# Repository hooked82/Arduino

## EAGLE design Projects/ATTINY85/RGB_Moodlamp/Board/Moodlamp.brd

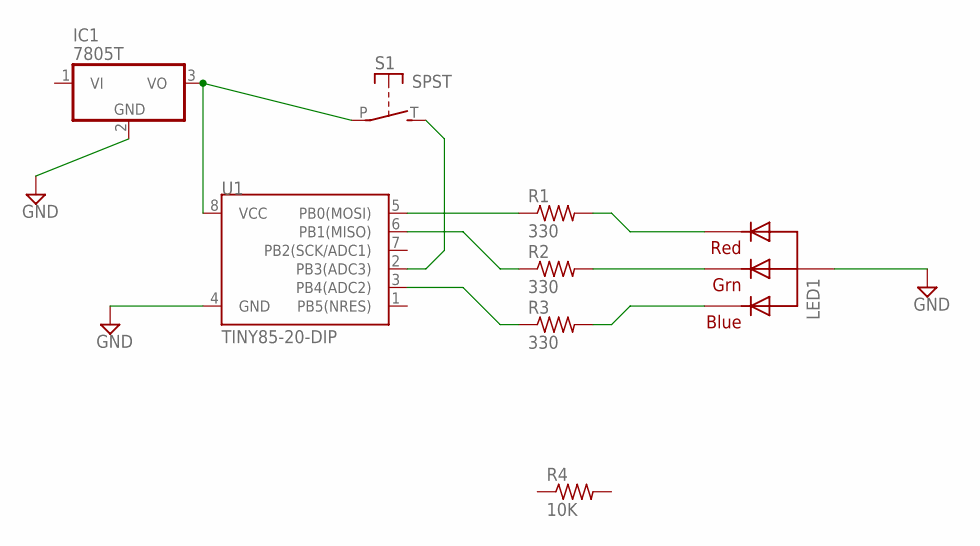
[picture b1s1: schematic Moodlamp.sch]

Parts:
IC1: 7805T; TO220H
LED1: RGBLED_CA-5MM; LED5MMRGB
R1, R2, R3: 330; 0207/10
R4: 10K; 0207/10
S1: SPST; JUDCOSPST
U1: TINY85-20-DIP; DIP08

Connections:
GND: IC1.2 (GND), LED1.2 (VCC), U1.4 (GND)
unnamed: LED1.1 (RED), R1.2
unnamed: LED1.3 (GREEN), R2.2
unnamed: LED1.4 (BLUE), R3.2
unnamed: R1.1, U1.5 (PB0(MOSI))
unnamed: R2.1, U1.6 (PB1(MISO))
unnamed: R3.1, U1.3 (PB4(ADC2))
unnamed: IC1.3 (VO), S1.P, U1.8 (VCC)
unnamed: S1.T (S), U1.2 (PB3(ADC3))

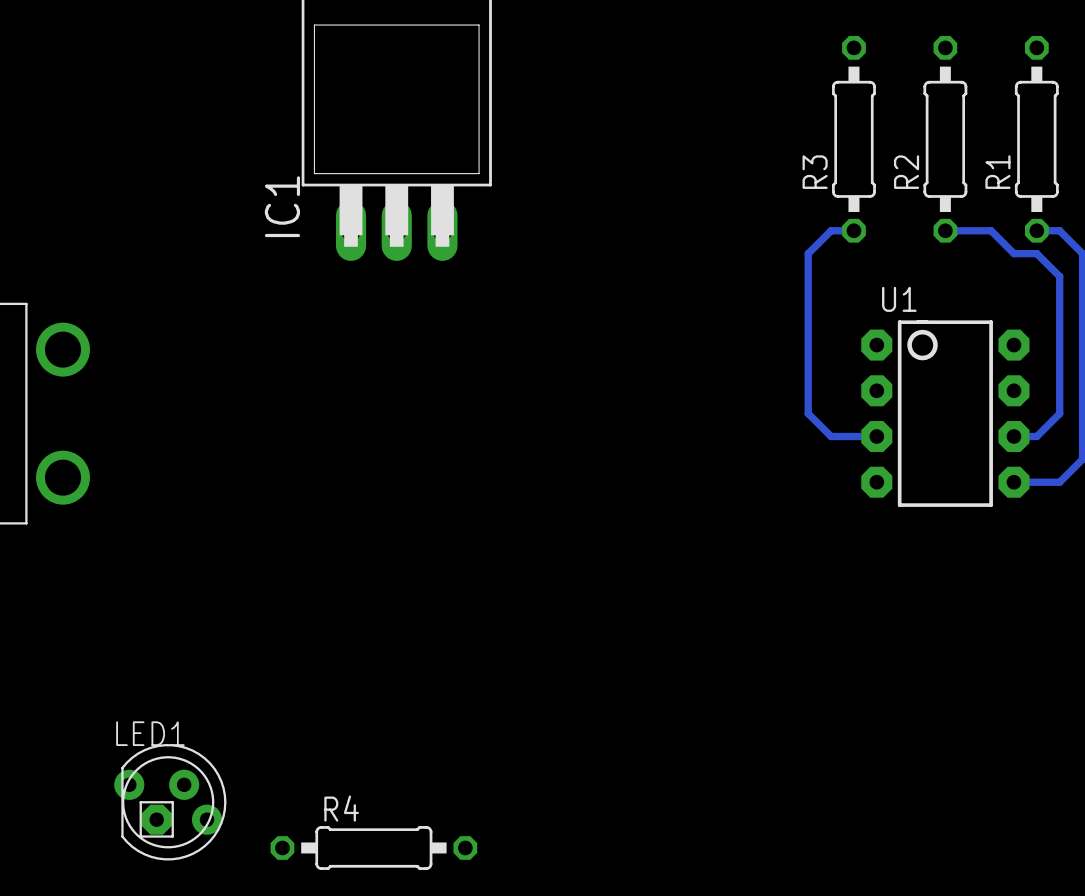
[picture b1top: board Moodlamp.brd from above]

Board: 2 copper layers, 8 parts (0 on the bottom side), 9 nets.

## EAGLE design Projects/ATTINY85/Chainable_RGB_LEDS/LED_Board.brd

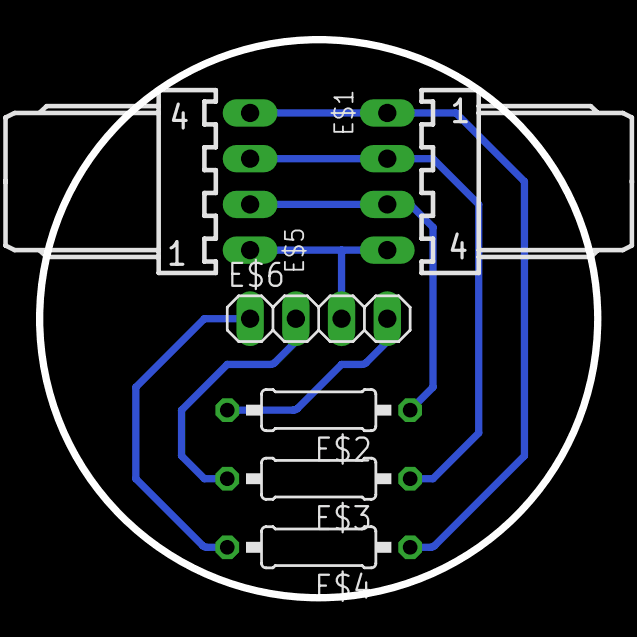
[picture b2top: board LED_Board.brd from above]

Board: 2 copper layers, 31.0 x 31.0 mm, 6 parts (0 on the bottom side), 7 nets.

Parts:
E$1, E$5: 7395-04
E$2, E$3, E$4: 0207/10
E$6: 1X04

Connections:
S$1: E$1.2, E$3.1, E$5.3
S$2: E$1.4, E$5.1, E$6.3
S$4: E$1.3, E$2.1, E$5.2
S$5: E$4.2, E$6.1
S$6: E$3.2, E$6.2
S$7: E$2.2, E$6.4
S$8: E$1.1, E$4.1, E$5.4

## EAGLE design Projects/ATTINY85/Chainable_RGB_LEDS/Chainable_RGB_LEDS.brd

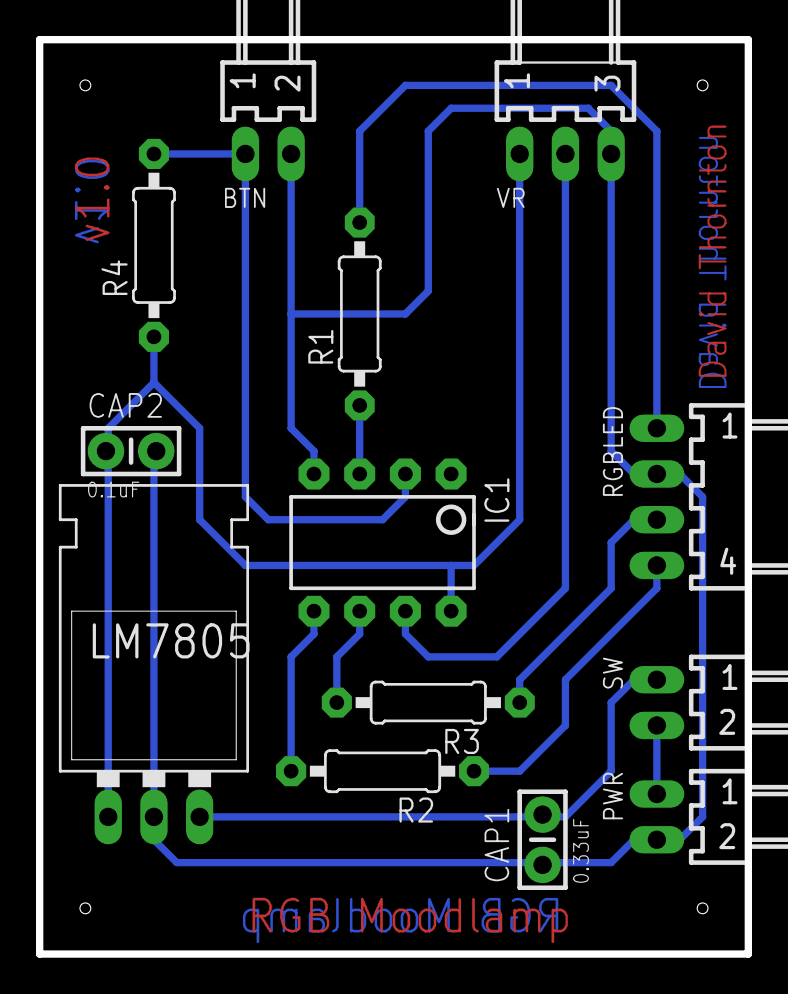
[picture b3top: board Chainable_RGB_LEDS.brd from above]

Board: 2 copper layers, 39.4 x 50.8 mm, 14 parts (0 on the bottom side), 12 nets.

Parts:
BTN: 7395-02
CAP1: 0.33uF; CAP-PTH-SMALL-KIT
CAP2: 0.1uF; CAP-PTH-SMALL-KIT
DRILEGEND: DRILEGEND
IC1: ATTINY85; DIP08
LM7805: VREG; TO-220-ALT
PWR: 7395-02
R1, R2, R3: 330R; 0207/10
R4: 10K; 0207/10
RGBLED: 7395-04
SW: 7395-02
VR: 7395-03

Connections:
S$1: LM7805.OUT, SW.1
S$2: PWR.1, SW.2
S$3: R1.2, RGBLED.1
S$6: IC1.7, VR.2
S$7: R3.1, RGBLED.3
S$8: IC1.6, R3.2
S$9: IC1.5, R2.2
S$10: R2.1, RGBLED.4
S$12: BTN.2, IC1.4, LM7805.GND, PWR.2, RGBLED.2, VR.3
S$13: IC1.8, LM7805.IN, R4.1, VR.1
S$14: IC1.3, R1.1
S$15: BTN.1, IC1.2, R4.2

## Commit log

2015-01-03 Creating initial folders
2015-01-03 ATTINY85 RGB Moodlamp Code/Schematics
2015-01-24 Adding new Eagle boards
2015-01-24 Add SparkFun Eagle Libraries
2015-01-25 v1.0 Board Completed
2015-01-25 v1.0 Connector Board Completed
2015-01-25 Exported Prints

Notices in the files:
parts and their libraries:
SparkFun-DigitalIC: Licensing: Creative Commons ShareAlike 4.0 International - https://creativecommons.org/licenses/by-sa/4.0
